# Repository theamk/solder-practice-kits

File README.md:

# Learn-to-solder practice boards

- Through-hole parts
- Low density
- Few components overall
- Few types of components

### License

This work is licensed under [Creative Commons Attribution-NonCommercial-ShareAlike 4.0 International License][cc-by-nc-sa].

[![CC BY-NC-SA 4.0][cc-by-nc-sa-image]][cc-by-nc-sa]
[![CC BY-NC-SA 4.0][cc-by-nc-sa-shield]][cc-by-nc-sa]

[cc-by-nc-sa]: http://creativecommons.org/licenses/by-nc-sa/4.0/
[cc-by-nc-sa-image]: https://licensebuttons.net/l/by-nc-sa/4.0/88x31.png
[cc-by-nc-sa-shield]: https://img.shields.io/badge/License-CC%20BY--NC--SA%204.0-lightgrey.svg

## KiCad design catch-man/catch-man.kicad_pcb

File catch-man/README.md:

# "catch-man" game

# Part list

### STC8G1K08A-36I-DIP8

In 2025-12, bought 10x for $3.44 (free choice shipping): [listing](https://www.aliexpress.us/item/3256807473048659.html)

STC8G1K17A-36I-DIP8 would be even better (more FLASH for program), but it was much more expensive.

### UI

- 12x 3mm/5mm LED (red/yellow/green recommended, no blue or white)
- 1x "12x12mm" tactile button
- 1x slide switch (SS12D00 or equivalent, 3 pins @ 2.5mm/2.54mm spacing)
- 1x single-position DIP slide switch,7.62mm spacing
- Piezo buzzer (passive, "1407", pin spacing 7.5mm or 7.6mm)
- CR2032, "shell" holder (BS-2032A but not all listing say this, look for 20mm inter-pin distance)

### Misc

- 1x DIP-8 socket
- 4x 1/8W resistors for LEDs... Perhaps 68 ohm for green, 100 ohm for red (maybe?)
- 1x 0.1u capacitor (disc, with 2.54mm pin spacing)

### Programming

You need to program STC8 chips. They accept regular serial TTL data, so you can get away with generic usb-serial.
The chip listens to instructions for first few mS after power-on, so you'll need a way to temporary disconnect
GND.

Those can be programmed before insertion, or you can use test clip for in-circuit programming
(the LEDs are connected so this is possible)

The easiest way to program is to use `pio run -t upload` in the firmware dir.
And alternative is to install stcgal and execute:
```
stcgal.py -P stc8g -p /dev/ttyUSB0 -t 11059 -a firmware/firmware.hex
```

# Testing/orders

### Revision 1

Ordered from JLCPCB 2025-12-24
- 5x, green color, "Lead-free HASL", everything else default
- Cost:
   - Merchandise Total:  $10.30
   - Shipping Estimate:  $10.90
   - (had some coupons which paid for it, would be about $22.50 otherwise)

Notes for next rev:
- See "Changes" for Revision 2 below
- Tested green LED + 68 ohm resistors.. looks good enough (on battery and 3.3v supply)
- For next time: the timer output is not hooked up to speaker
- Programming pin is hooked to speaker. When speaker is bypassed, this makes in-circuit programming impossible
  Either move to a different pin, or add a "mute" switch
- Speaker transistor is redundant, tested with directly-driven piezo speaker, sounds just fine
    - Piezo speaker model unknown, measured: D=14mm H=7mm Spacing=7.6mm C=13.6nF
    - Dynamic speaker (say 16 ohm) is 190mA, way too much for CR2032 anyway
- Let's make eyes be different - rectangular LED, or bigger, or smaller...

### Revision 1.1

Changes:
- Put "catch-man" in large font on front side (this required moving speaker down)
- Set "thing" outlines to be much thicker
- Re-route front traces to not intersect silkscreen lines.. in general, move more stuff to the back, via's are neat
- Removed transistor, added mute switch instead
- Updated speaker spacing to 7.6mm
- Added a single mounting hole in the very center

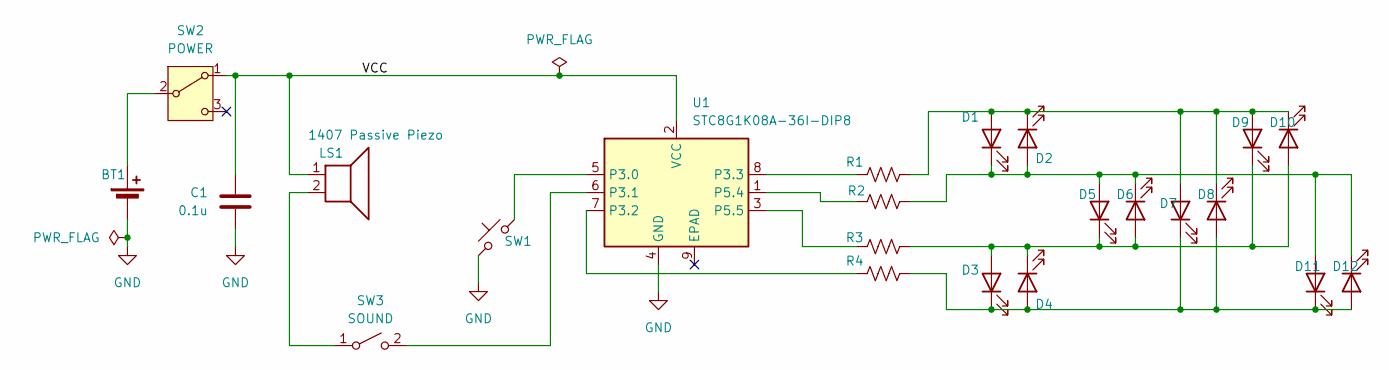
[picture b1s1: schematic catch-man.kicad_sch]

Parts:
BT1: Battery_Cell; CR2032-THT-retainer
C1: 0.1u; C_Disc_D3.0mm_W1.6mm_P2.50mm
D1, D2, D3, D4, D5, D6, D7, D8, D9, D10, D11, D12: LED; LED_D5.0mm
LS1: 1407 Passive Piezo; Buzzer_15x7.5RM7.6
R1, R2, R3, R4: 120; R_Axial_DIN0204_L3.6mm_D1.6mm_P7.62mm_Horizontal
SW1: SW_Push_45deg; SW_PUSH-12mm
SW2: POWER; SW_Slide-03_Wuerth-WS-SLTV_10x2.5x6.4_P2.54mm
SW3: SOUND; SW_DIP_SPSTx01_Slide_9.78x4.72mm_W7.62mm_P2.54mm
U1: STC8G1K08A-36I-DIP8; DIP-8_W7.62mm_LongPads

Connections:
/VCC: C1.1, LS1.1, SW2.1 (A), U1.2 (VCC)
GND: BT1.2 (-), C1.2, SW1.1, U1.4 (GND)
unnamed: BT1.1 (+), SW2.2 (B)
unnamed: D1.2 (A), D2.1 (K), D7.2 (A), D8.1 (K), D9.2 (A), D10.1 (K), R1.2
unnamed: D1.1 (K), D2.2 (A), D5.2 (A), D6.1 (K), D11.2 (A), D12.1 (K), R2.2
unnamed: D3.2 (A), D4.1 (K), D5.1 (K), D6.2 (A), D9.1 (K), D10.2 (A), R3.2
unnamed: D3.1 (K), D4.2 (A), D7.1 (K), D8.2 (A), D11.1 (K), D12.2 (A), R4.2
unnamed: LS1.2, SW3.1 (A)
unnamed: SW3.2 (B), U1.6 (P3.1)
unnamed: SW1.2, U1.5 (P3.0)
unnamed: R4.1, U1.7 (P3.2)
unnamed: R1.1, U1.8 (P3.3)
unnamed: R2.1, U1.1 (P5.4)
unnamed: R3.1, U1.3 (P5.5)

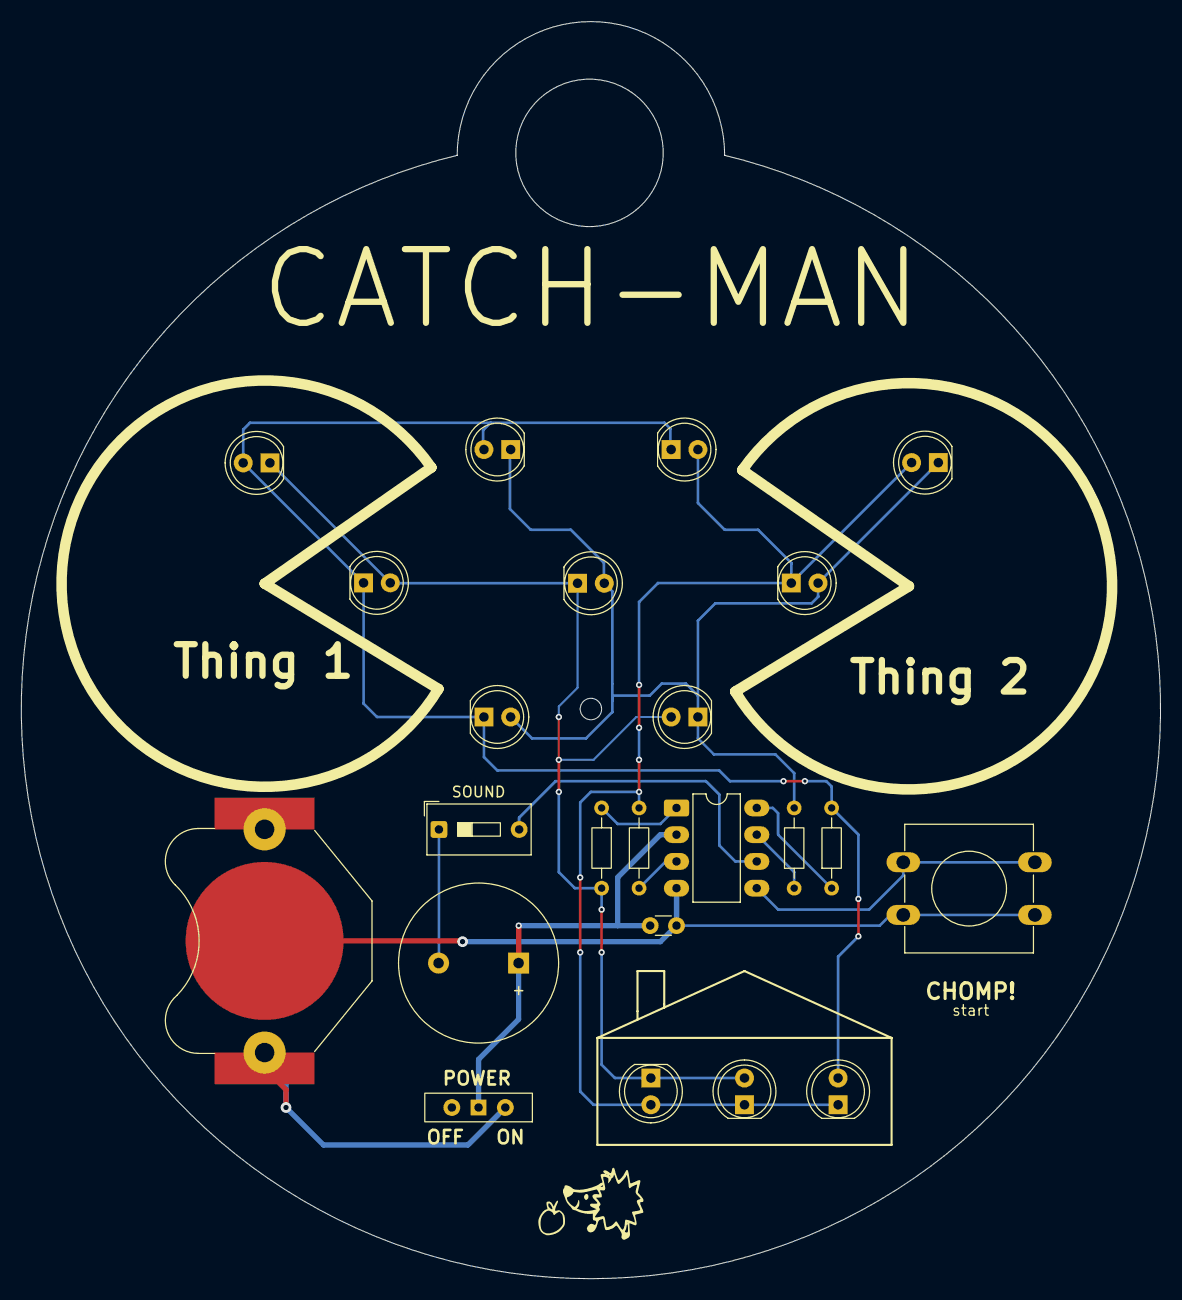
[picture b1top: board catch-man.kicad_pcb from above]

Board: 2 copper layers, 108.2 x 119.4 mm, 23 parts (0 on the bottom side), 14 nets.

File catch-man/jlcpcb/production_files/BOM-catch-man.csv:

Comment,Designator,Footprint,LCSC,Quantity
1407 Passive Piezo,LS1,Buzzer_15x7.5RM7.6,,1
STC8G1K08A-36I-DIP8,U1,DIP-8_W7.62mm_LongPads,,1
SW_Push_45deg,SW1,SW_PUSH-12mm,,1
120,R4,R_Axial_DIN0204_L3.6mm_D1.6mm_P7.62mm_Horizontal,,1
120,R3,R_Axial_DIN0204_L3.6mm_D1.6mm_P7.62mm_Horizontal,,1
120,R2,R_Axial_DIN0204_L3.6mm_D1.6mm_P7.62mm_Horizontal,,1
120,R1,R_Axial_DIN0204_L3.6mm_D1.6mm_P7.62mm_Horizontal,,1
LED,D12,LED_D5.0mm,,1
LED,D11,LED_D5.0mm,,1
LED,D10,LED_D5.0mm,,1
LED,D9,LED_D5.0mm,,1
LED,D8,LED_D5.0mm,,1
LED,D7,LED_D5.0mm,,1
LED,D6,LED_D5.0mm,,1
LED,D5,LED_D5.0mm,,1
LED,D4,LED_D5.0mm,,1
LED,D3,LED_D5.0mm,,1
LED,D2,LED_D5.0mm,,1
LED,D1,LED_D5.0mm,,1
Battery_Cell,BT1,CR2032-THT-retainer,,1
POWER,SW2,SW_Slide-03_Wuerth-WS-SLTV_10x2.5x6.4_P2.54mm,,1
0.1u,C1,C_Disc_D3.0mm_W1.6mm_P2.50mm,,1
SOUND,SW3,SW_DIP_SPSTx01_Slide_9.78x4.72mm_W7.62mm_P2.54mm,,1

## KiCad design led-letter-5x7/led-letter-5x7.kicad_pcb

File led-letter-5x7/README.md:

LED letter badge

# Part list

### LED matrix 5x7, with 1.9mm pixel (pretty small)

Either common anode or common cathode can work, based on software
- Pretty hard to source, I found 1 source on Aliexpress:
  ["10PCS x 1.9MM 5X7 White Blue White Red Common Cathode/Anode LED Dot Matrix Digital Tube Module 757AS 757BS LED Display Module"]([https://www.aliexpress.us/item/2251801143009542.html)
   - Sold by [KESUN KESUN](https://www.aliexpress.com/store/1100399907)
   - 2025-12 Price was $8.26(red), $11.02 (yellow), $10.83 (green) + shipping
     I paid $30.38 for 20x (Yellow Anode 757BY + Green Cathode 757AG)
- Other option is https://www.aliexpress.us/item/3256807420112720.html - same description, very similar price.
  I suspect it's the same store.

### STC8G1K17-38I-DIP16

In 2025-12, bought 5x for $4.00 (free "choice" shipping), but the listing is already gone:
- [STC8G1K17 STC8G1K17-38I DIP16 STC 8G1K17-38I Single Chip Microcontroller IC Controller Chip STC8G1K17-38I-DIP16 Original](https://www.aliexpress.us/item/3256807299744981.html)
- there is new one even cheaper (5x for $3.75)

### Mechanicals

- 3x buttons (Tactile Switch 3.5x6 2-pin DIP)
   - 2025-12 [example](https://www.aliexpress.us/item/3256801442870232.html?), $2.14/50x, free ship
- 1x slide switch (SS12D00 or equivalent, 3 pins @ 2.5mm/2.54mm spacing)
- Power:
   - For CR2032, "shell" holder (BS-2032A but not all listing say this, look for 20mm inter-pin distance)
   - For 3xAAA, PH2.0 connector + 3xAAA battery box with switch and PH2.0 connector

### Misc parts

- 1x DIP-16 socket
- 7x 1.8W resistors... Perhaps 100 ohm? Need to test brightness, depends on color
- 1x 0.1u capacitor (disc, with 2.54mm pin spacing)
- 2x small diodes (any will work, as long as they fit in the hole)

### Programming

You need to program STC8 chips. They accept regular serial TTL data, so you can get away with generic usb-serial.
The chip listens to instructions for first few mS after power-on, so you'll need a way to temproary disconnect
GND.

For advanced usage, you can get 4-pin 2.54mm clip and have auto-power-off circuit.

# Testing/orders

### Revision 1

Ordered from JLCPCB 2025-12-27
- 5x, green color, "Lead-free HASL", everything else default
- Cost:
   - Merchandise Total:  $3.10
   - Shipping Estimate:  $3.12  (was $7.28, but got some coupon)
   - Sales Tax:          $0.39
   - Grand Total:        $6.61

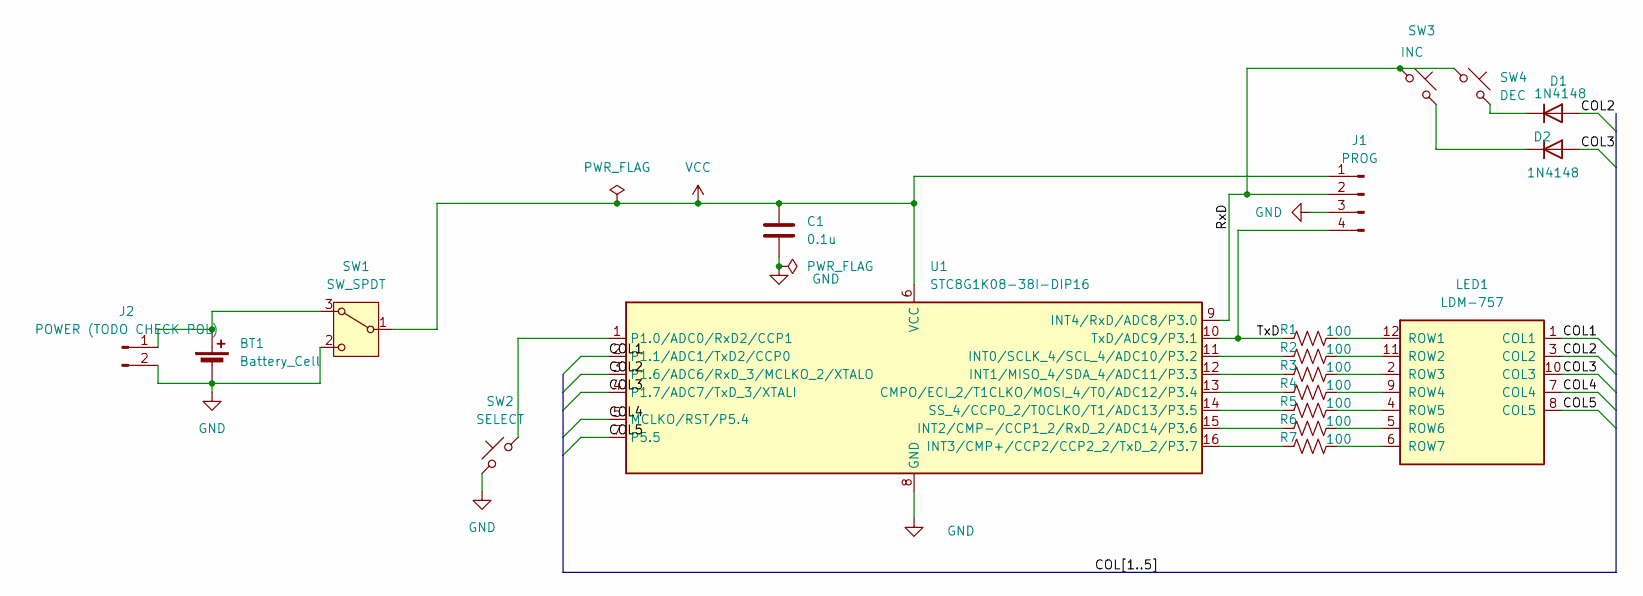
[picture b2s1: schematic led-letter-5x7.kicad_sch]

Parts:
BT1: Battery_Cell; CR2032-THT
C1: 0.1u; C_Disc_D3.0mm_W1.6mm_P2.50mm
D1, D2: 1N4148; D_DO-35_SOD27_P7.62mm_Horizontal
J1: PROG; PinHeader_1x04_P2.54mm_Vertical
J2: POWER (TODO CHECK POL); JST_PH_B2B-PH-K_1x02_P2.00mm_Vertical
LED1: LDM-757; LDL-757-5x7-1.9mm-led
R1, R2, R3, R4, R5, R6, R7: 100; R_Axial_DIN0204_L3.6mm_D1.6mm_P7.62mm_Horizontal
SW1: SW_SPDT; SW_Slide-03_Wuerth-WS-SLTV_10x2.5x6.4_P2.54mm
SW2: SELECT; SW_PUSH_1P1T_6x3.5mm_H4.3_APEM_MJTP1243
SW3: INC; SW_PUSH_1P1T_6x3.5mm_H4.3_APEM_MJTP1243
SW4: DEC; SW_PUSH_1P1T_6x3.5mm_H4.3_APEM_MJTP1243
U1: STC8G1K08-38I-DIP16; DIP-16_W7.62mm_Socket_LongPads

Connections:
/COL1: LED1.1 (COL1), U1.2 (P1.1/ADC1/TxD2/CCP0)
/COL2: D1.2 (A), LED1.3 (COL2), U1.3 (P1.6/ADC6/RxD_3/MCLKO_2/XTALO)
/COL3: D2.2 (A), LED1.10 (COL3), U1.4 (P1.7/ADC7/TxD_3/XTALI)
/COL4: LED1.7 (COL4), U1.5 (MCLKO/RST/P5.4)
/COL5: LED1.8 (COL5), U1.7 (P5.5)
/RxD: J1.2, SW3.2, SW4.2, U1.9 (INT4/RxD/ADC8/P3.0)
/TxD: J1.4, R1.1, U1.10 (TxD/ADC9/P3.1)
GND: BT1.2 (-), C1.2, J1.3, J2.2, SW1.2 (C), SW2.2, U1.8 (GND)
unnamed: BT1.1 (+), J2.1, SW1.3 (A)
unnamed: D1.1 (K), SW4.1
unnamed: D2.1 (K), SW3.1
unnamed: LED1.12 (ROW1), R1.2
unnamed: LED1.11 (ROW2), R2.2
unnamed: LED1.2 (ROW3), R3.2
unnamed: LED1.9 (ROW4), R4.2
unnamed: LED1.4 (ROW5), R5.2
unnamed: LED1.5 (ROW6), R6.2
unnamed: LED1.6 (ROW7), R7.2
unnamed: R4.1, U1.13 (CMPO/ECI_2/T1CLKO/MOSI_4/T0/ADC12/P3.4)
unnamed: R2.1, U1.11 (INT0/SCLK_4/SCL_4/ADC10/P3.2)
unnamed: R3.1, U1.12 (INT1/MISO_4/SDA_4/ADC11/P3.3)
unnamed: R6.1, U1.15 (INT2/CMP-/CCP1_2/RxD_2/ADC14/P3.6)
unnamed: R7.1, U1.16 (INT3/CMP+/CCP2/CCP2_2/TxD_2/P3.7)
unnamed: SW2.1, U1.1 (P1.0/ADC0/RxD2/CCP1)
unnamed: R5.1, U1.14 (SS_4/CCP0_2/T0CLKO/T1/ADC13/P3.5)
VCC: C1.1, J1.1, SW1.1 (B), U1.6 (VCC)

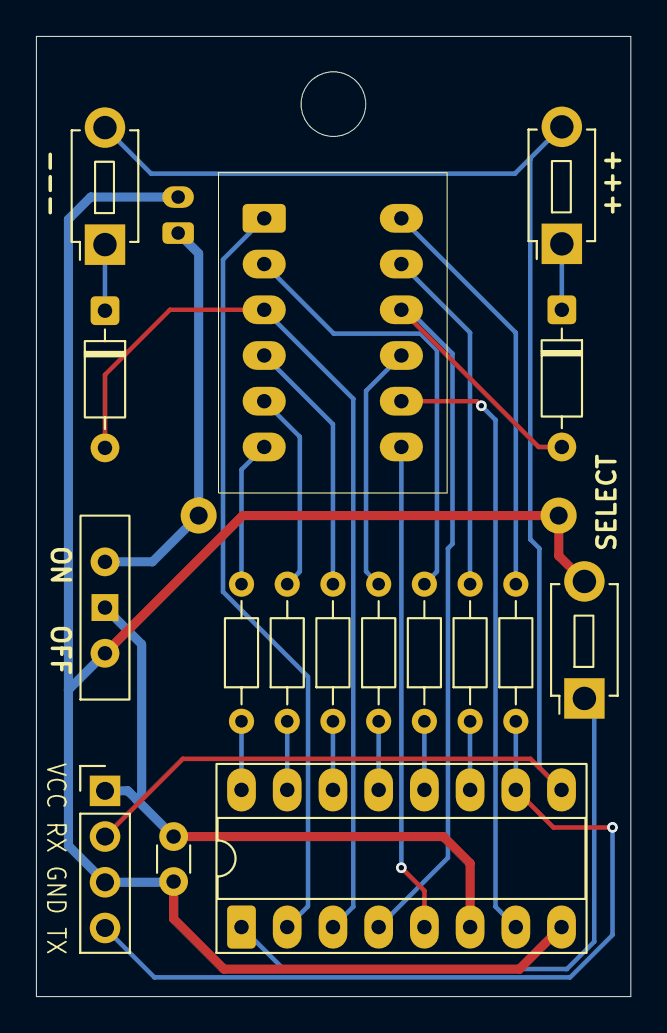
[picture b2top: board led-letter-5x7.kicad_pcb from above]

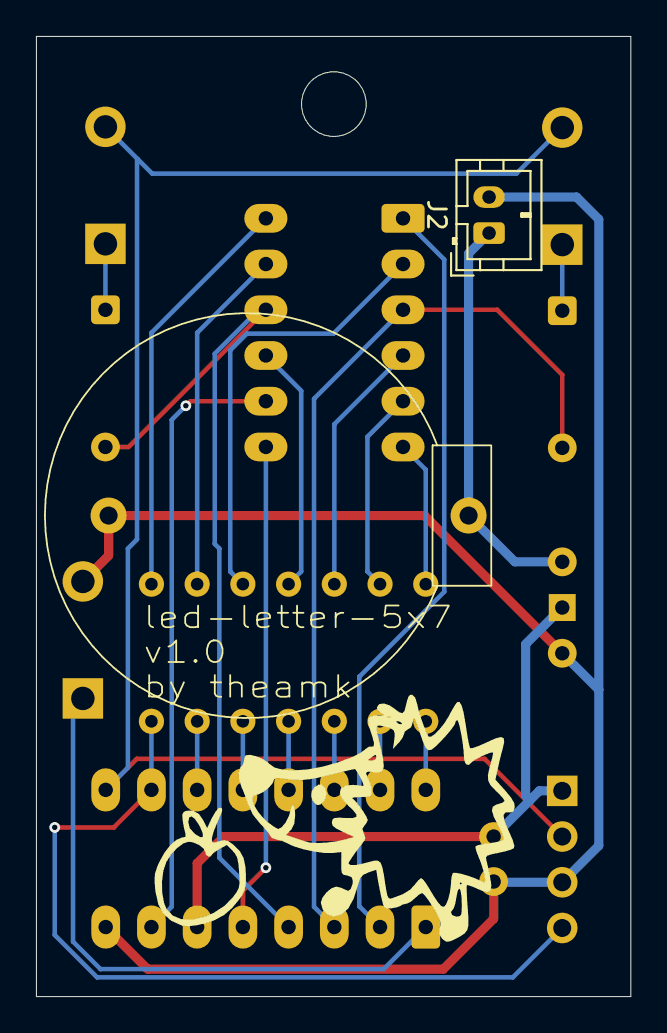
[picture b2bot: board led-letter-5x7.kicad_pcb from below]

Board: 2 copper layers, 33.0 x 53.3 mm, 19 parts (2 on the bottom side), 26 nets.

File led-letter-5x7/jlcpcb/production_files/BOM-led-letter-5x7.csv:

Comment,Designator,Footprint,LCSC,Quantity
100,R5,R_Axial_DIN0204_L3.6mm_D1.6mm_P7.62mm_Horizontal,,1
100,R7,R_Axial_DIN0204_L3.6mm_D1.6mm_P7.62mm_Horizontal,,1
100,R2,R_Axial_DIN0204_L3.6mm_D1.6mm_P7.62mm_Horizontal,,1
100,R4,R_Axial_DIN0204_L3.6mm_D1.6mm_P7.62mm_Horizontal,,1
100,R1,R_Axial_DIN0204_L3.6mm_D1.6mm_P7.62mm_Horizontal,,1
Battery_Cell,BT1,CR2032-THT,,1
100,R3,R_Axial_DIN0204_L3.6mm_D1.6mm_P7.62mm_Horizontal,,1
100,R6,R_Axial_DIN0204_L3.6mm_D1.6mm_P7.62mm_Horizontal,,1
DEC,SW4,SW_PUSH_1P1T_6x3.5mm_H4.3_APEM_MJTP1243,,1
1N4148,D2,D_DO-35_SOD27_P7.62mm_Horizontal,,1
1N4148,D1,D_DO-35_SOD27_P7.62mm_Horizontal,,1
STC8G1K08-38I-DIP16,U1,DIP-16_W7.62mm_Socket_LongPads,,1
INC,SW3,SW_PUSH_1P1T_6x3.5mm_H4.3_APEM_MJTP1243,,1
SELECT,SW2,SW_PUSH_1P1T_6x3.5mm_H4.3_APEM_MJTP1243,,1
SW_SPDT,SW1,SW_Slide-03_Wuerth-WS-SLTV_10x2.5x6.4_P2.54mm,,1
LDM-757,LED1,LDL-757-5x7-1.9mm-led,,1
POWER (TODO CHECK POL),J2,JST_PH_B2B-PH-K_1x02_P2.00mm_Vertical,,1
PROG,J1,PinHeader_1x04_P2.54mm_Vertical,,1
0.1u,C1,C_Disc_D3.0mm_W1.6mm_P2.50mm,,1

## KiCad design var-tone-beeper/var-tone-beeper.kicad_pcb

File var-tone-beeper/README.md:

Learn-to-solder kit: var-tone-beeper
"variable tone beeper"
=====

Part list:
(prices as of 2025-03)

PCB 10x ($22.46/10x -> $2.24/each)
- black, lead-free

DIP-8 chip socket ($2.84/25 -> $0.11/each)
+ NE555P chip (sold as pair)
- socket optional but recommended
- https://www.aliexpress.us/item/3256805880822598.html
- note: TLC55CP provides a very quiet sound

23mm speaker (($7.50 + $3.16)/10 = $1.07/each)
- 1508/2308/3013 passive direct plug small speaker 8 ohm 1 watt foot distance 10m fingerprint lock speaker 23*8mm 10PCS
- https://www.aliexpress.us/item/2251832605561774.html

3xAAA PC mount battery box ($4.14/10x -> $0.41/each)
- https://www.aliexpress.us/item/3256806088417831.html

Potentiometer, PC mount vertical, 500K "A" taper ($3.12/10x -> $0.31 each)
- "R097 RK097 Precision Potentiometer Vertical Single Pole with Bracket Shaft 15mm Without Notches 3 Pins A5K 50K 100K 500K"
- https://www.aliexpress.us/item/3256806835661913.html
- Not the best - too tall. Would love to find lower profile.

Potentiometer knob ($1.45/20x -> $0.07/each)
- "WH148 Potentiometer Knob Kit Plastic Knobs Cap 15*17MM Shaft Hole 6MM AG2"
- https://www.aliexpress.us/item/3256805921143559.html

Resistor 1K 1/8w (or 1/8w)
- Stock now, future: https://www.aliexpress.com/item/3256802183266089.html

Capacitor 0.1uF, 5mm pin spacing

Button 14mm

Button cap (colored)

2x Screw M2x6 "ultra thin head" + 2x nut M2

total (excluding battery): ??

====

V1 notes:
- We require 1/8W resistor -> increase footprint to accept 1/4W as well
- Potentiometer lugs slots are too small.
- Holes for IC socket pretty small. Workable but maybe increase for beginners?
- Maybe decrease hole size around battery holder if we plan to keep M2 screws?
  (or keep it.. the current holes work great with M3 screws)
- Need to find log (A504) resistor and test it

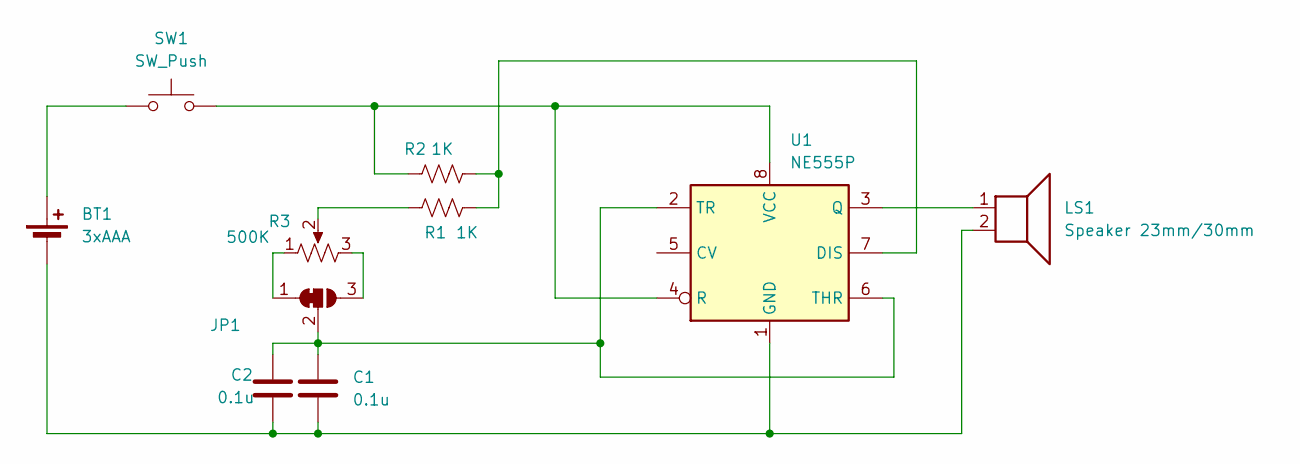
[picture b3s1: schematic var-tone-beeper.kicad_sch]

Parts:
BT1: 3xAAA; BatteryHolder_Generic_3xAAA
C1, C2: 0.1u; C_Disc_D3.4mm_W2.1mm_P2.50mm
JP1: SolderJumper_3_Bridged12; SolderJumper-3_P1.3mm_Bridged12_RoundedPad1.0x1.5mm
LS1: Speaker 23mm/30mm; PC-mnt-speaker-23-mm
R1, R2: 1K; R_Axial_DIN0204_L3.6mm_D1.6mm_P7.62mm_Horizontal
R3: 500K; Potentiometer_Alpha_RD901F-40-00D_Single_Vertical
SW1: SW_Push; SW_PUSH-12mm
U1: NE555P; DIP-8_W7.62mm

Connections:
unnamed: BT1.1 (+), SW1.1
unnamed: BT1.2 (-), C1.2, C2.2, LS1.2, U1.1 (GND)
unnamed: JP1.1 (A), R3.1
unnamed: JP1.3 (B), R3.3
unnamed: C1.1, C2.1, JP1.2 (C), U1.2 (TR), U1.6 (THR)
unnamed: R1.2, R3.2
unnamed: R1.1, R2.2, U1.7 (DIS)
unnamed: LS1.1, U1.3 (Q)
unnamed: R2.1, SW1.2, U1.4 (R), U1.8 (VCC)

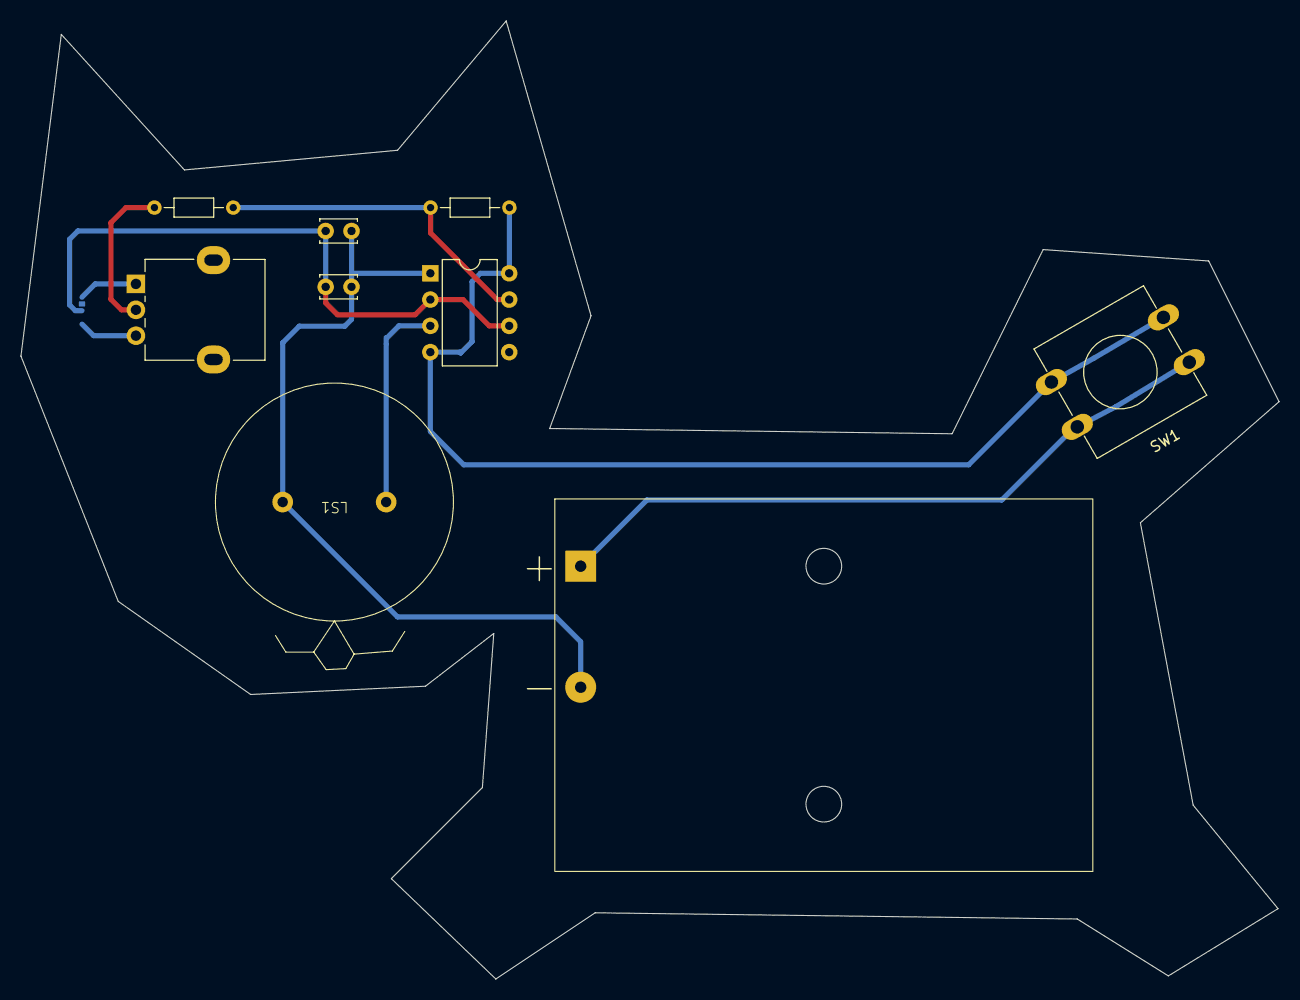
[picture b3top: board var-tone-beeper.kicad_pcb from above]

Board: 2 copper layers, 121.6 x 92.6 mm, 10 parts (1 on the bottom side), 9 nets.

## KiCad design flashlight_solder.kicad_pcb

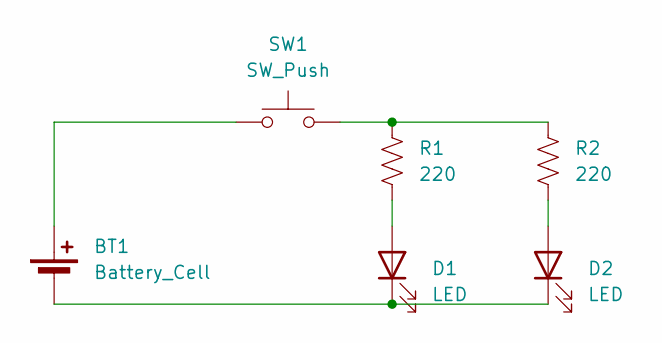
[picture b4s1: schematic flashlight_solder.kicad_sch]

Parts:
BT1: Battery_Cell; CR2032-THT
D1, D2: LED; LED_SideEmitter_Rectangular_W4.5mm_H1.6mm
R1, R2: 220; R_Axial_DIN0207_L6.3mm_D2.5mm_P10.16mm_Horizontal
SW1: SW_Push; SW_PUSH_6mm

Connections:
unnamed: BT1.1 (+), SW1.1
unnamed: BT1.2 (-), D1.1 (K), D2.1 (K)
unnamed: D1.2 (A), R1.2
unnamed: D2.2 (A), R2.2
unnamed: R1.1, R2.1, SW1.2

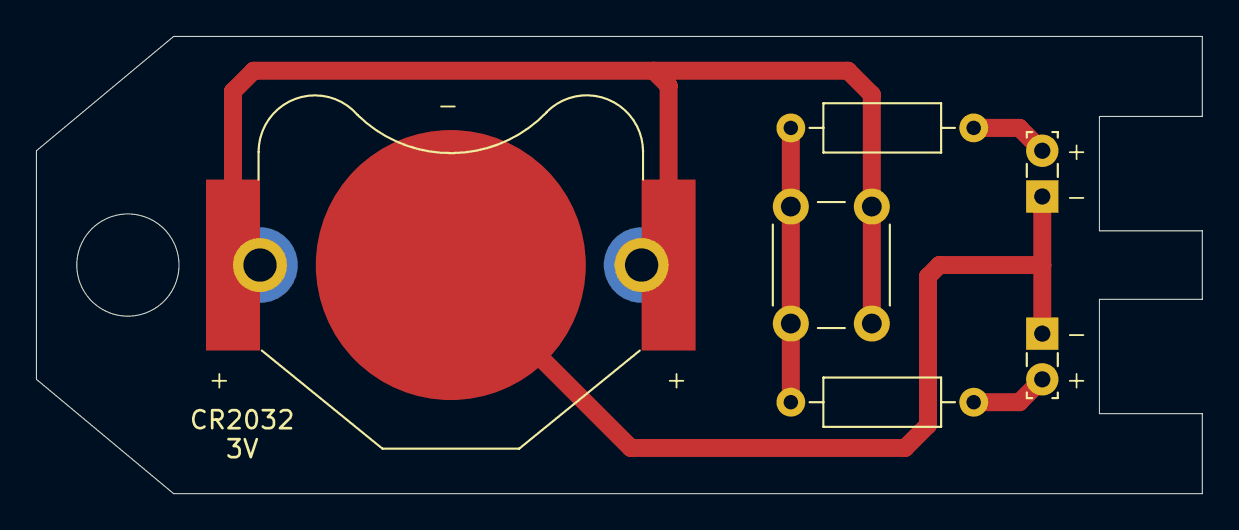
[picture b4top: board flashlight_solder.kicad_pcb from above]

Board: 2 copper layers, 64.8 x 25.4 mm, 6 parts (0 on the bottom side), 5 nets.

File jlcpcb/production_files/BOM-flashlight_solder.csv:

Comment,Designator,Footprint,LCSC,Quantity
Battery_Cell,BT1,CR2032-THT-retainer,,1
SW_Push,SW1,SW_PUSH_6mm,,1
220,R1,R_Axial_DIN0207_L6.3mm_D2.5mm_P10.16mm_Horizontal,,1
LED,D2,LED_SideEmitter_Rectangular_W4.5mm_H1.6mm,,1
LED,D1,LED_SideEmitter_Rectangular_W4.5mm_H1.6mm,,1
220,R2,R_Axial_DIN0207_L6.3mm_D2.5mm_P10.16mm_Horizontal,,1

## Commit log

2024-12-22 Initial commit
    Paper printout indicated some problems, like button
    being too close to batteries
2024-12-22 Update board: - add keyhole - move button further front
2024-12-22 Change to different battery holder part
    - lower profile
    - battery less likely to fall out
2025-03-08 Fixed battery footprint, ordered
    ordered @ jlcpcb: 30x purple lead-free for
    total $11.26 (incl $9.19 boards, $1.50 shipping, tax)
2025-03-15 Move flashlight-related files to a subdirectory
2025-03-15 Move parts library to toplevel
2025-03-16 2nd board: variable tone beeper
    board is not fully layed out, checkout jlcpcb cost
    which is $23.60 + $13.42 shipping for 10 boards
    (119x195 mm PCB size)
2025-03-16 var-tone-beeper bugfixes
    fixed schematics bug
    switched to 23mm speaker only
    made proper footprint for batttery box
2025-03-17 ver-tone-beeper: v1 ordered
    Reduced board size
    Ordered
    JLCPCB cost: 10x for $14.10 + $8.36 shipping/tax
2025-12-07 Update var-tone-beeper README with part list, v1 notes
2025-12-07 Add license: CC-BY-NC-SA
2025-12-07 Add auto-generated board exports
2025-12-24 New project: catch-man
    Overall parts placement, no layout yet
2025-12-24 catch-man: v1
    Finished layout, centered parts
2025-12-28 catch-man v1: done, ordered
    Add 2nd footprint for speaker - not sure which one will work
    best
    Add README.md
2025-12-28 new project: led-letter-5x7
    Progress checkpoint - this version is too small,
    battery holder can't be mounted properly and
    blocks everything
2025-12-28 led-letter-5x7: v1 done, ordered
    Moved battery to the bottom
    Make outline more interesting
    Added README with parts list
2026-01-10 catch-man firware: test code
    Start on firmware, figure out platformio build tricks for
    small STC8G chips.
    Write some test code which blinks lights and sounds beeper.
2026-01-11 catch-man firmware: first version
    Factor out hw code into separate file
    Make basic game mechanics, although there is no
    "win" or "lose" conditions yet, nor there is any music
2026-01-11 catch-man firmware: add sounds
    They really make game much nicer.
2026-01-12 catch-man firmware: add levels
    Also bix bug with button pullup
    Also update README about speaker connection
2026-01-12 catch-man firmware: make levels easier
    Also add super-easy "level 0", just to help people get started
2026-01-12 catch-man: add backplate model v1
    It's pretty loose and we have no way to mount, but it's still
    useful.
2026-01-13 catch-man: start on board redesign
    To keep things simple, don't change connection pinout, duplicate
    manual changes on existing protype
    The "catch-man" caption is not big enough yet, we'll want to move it
2026-01-14 catch-man: board v1.1
    Moved speaker to the bottom, added large text on top.
    Re-routed bottom section.
    Also fixed CR2032-THT-retainer part so it does not throw
    as much DRC errors.
2026-01-17 catch-man: board update
2026-01-24 catchman firmware: add victory screen
    If level 3 is completed, player is shown a "victory screen",
    where LEDs flash in special pattern and button plays music.
    The only way to exit out of it is power cycle.
